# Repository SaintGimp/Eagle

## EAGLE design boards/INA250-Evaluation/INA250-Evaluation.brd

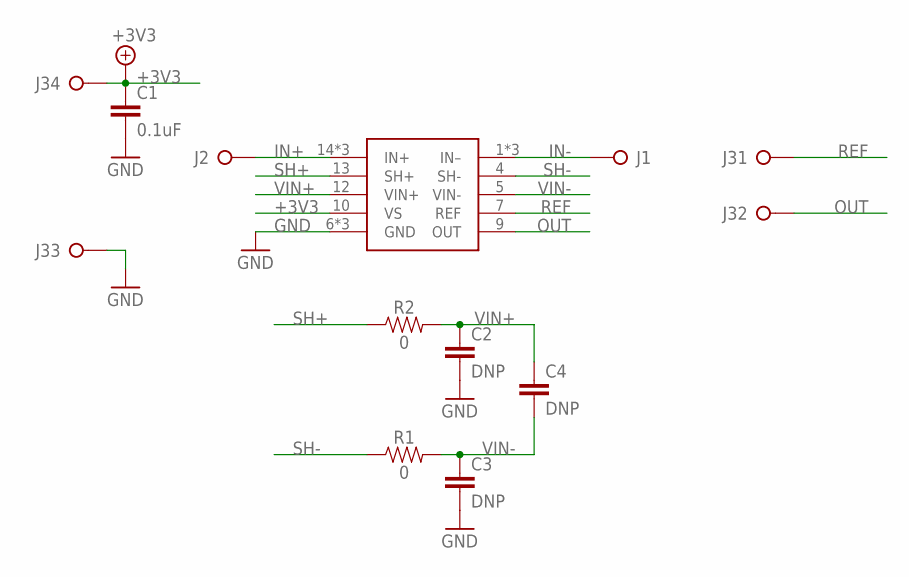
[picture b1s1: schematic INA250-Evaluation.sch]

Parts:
C1: 0.1uF; CAPACITOR-0805
C2, C3, C4: DNP; CAPACITOR-0805
IC1: INA250; TSSOP-16
J1, J2: PINHD-1X1BIG; 1X01-BIG
J3: PINHD-1X4; 1X04
R1, R2: 0; RESISTOR-0805

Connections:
+3V3: C1.1, IC1.10 (VS), J3.4
GND: C1.2, C2.2, C3.2, IC1.6 (GND), IC1.8 (GND), IC1.11 (GND), J3.3
IN+: IC1.14 (IN+), IC1.15 (IN+), IC1.16 (IN+), J2.1
IN-: IC1.1 (IN–), IC1.2 (IN–), IC1.3 (IN–), J1.1
OUT: IC1.9 (OUT), J3.2
REF: IC1.7 (REF), J3.1
SH+: IC1.13 (SH+), R2.1
SH-: IC1.4 (SH-), R1.1
VIN+: C2.1, C4.1, IC1.12 (VIN+), R2.2
VIN-: C3.1, C4.2, IC1.5 (VIN-), R1.2

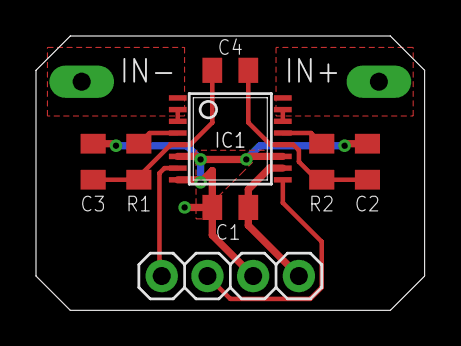
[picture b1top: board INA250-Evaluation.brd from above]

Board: 2 copper layers, 21.6 x 15.2 mm, 10 parts (0 on the bottom side), 10 nets.

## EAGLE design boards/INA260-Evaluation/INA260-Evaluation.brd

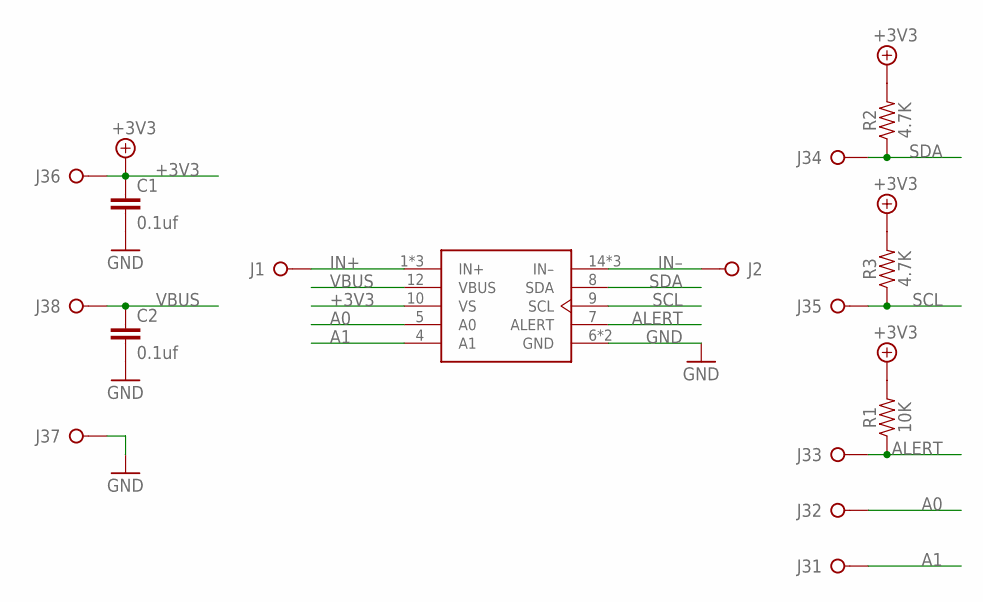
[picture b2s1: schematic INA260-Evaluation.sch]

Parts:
C1, C2: 0.1uf; CAPACITOR-0805
IC1: INA260; TSSOP-16
J1, J2: PINHD-1X1BIG; 1X01-BIG
J3: PINHD-1X8; 1X08
R1: 10K; RESISTOR-0805
R2, R3: 4.7K; RESISTOR-0805

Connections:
+3V3: C1.1, IC1.10 (VS), J3.6, R1.2, R2.2, R3.2
A0: IC1.5 (A0), J3.2
A1: IC1.4 (A1), J3.1
ALERT: IC1.7 (ALERT), J3.3, R1.1
GND: C1.2, C2.2, IC1.6 (GND), IC1.11 (GND), J3.7
IN+: IC1.1 (IN+), IC1.2 (IN+), IC1.3 (IN+), J1.1
IN–: IC1.14 (IN–), IC1.15 (IN–), IC1.16 (IN–), J2.1
SCL: IC1.9 (SCL), J3.5, R3.1
SDA: IC1.8 (SDA), J3.4, R2.1
VBUS: C2.1, IC1.12 (VBUS), J3.8

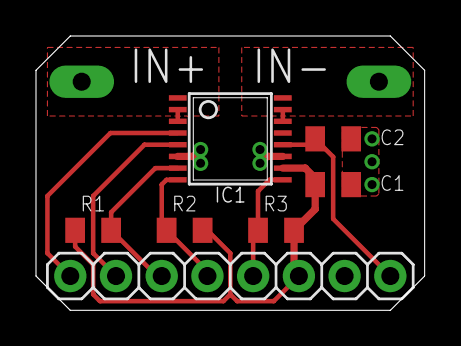
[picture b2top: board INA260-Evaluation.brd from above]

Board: 2 copper layers, 21.6 x 15.2 mm, 9 parts (0 on the bottom side), 10 nets.

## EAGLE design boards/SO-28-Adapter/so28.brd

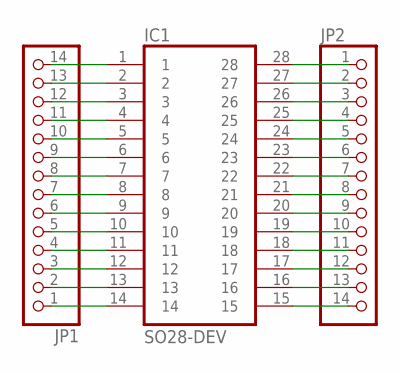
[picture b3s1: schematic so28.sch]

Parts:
IC1: SO28-DEV; SO28W
JP1, JP2: PINHD-1X14; 1X14

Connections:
unnamed: IC1.1, JP1.14
unnamed: IC1.2, JP1.13
unnamed: IC1.3, JP1.12
unnamed: IC1.4, JP1.11
unnamed: IC1.5, JP1.10
unnamed: IC1.6, JP1.9
unnamed: IC1.7, JP1.8
unnamed: IC1.8, JP1.7
unnamed: IC1.9, JP1.6
unnamed: IC1.10, JP1.5
unnamed: IC1.11, JP1.4
unnamed: IC1.12, JP1.3
unnamed: IC1.13, JP1.2
unnamed: IC1.14, JP1.1
unnamed: IC1.15, JP2.14
unnamed: IC1.16, JP2.13
unnamed: IC1.17, JP2.12
unnamed: IC1.18, JP2.11
unnamed: IC1.19, JP2.10
unnamed: IC1.20, JP2.9
unnamed: IC1.21, JP2.8
unnamed: IC1.22, JP2.7
unnamed: IC1.23, JP2.6
unnamed: IC1.24, JP2.5
unnamed: IC1.25, JP2.4
unnamed: IC1.26, JP2.3
unnamed: IC1.27, JP2.2
unnamed: IC1.28, JP2.1

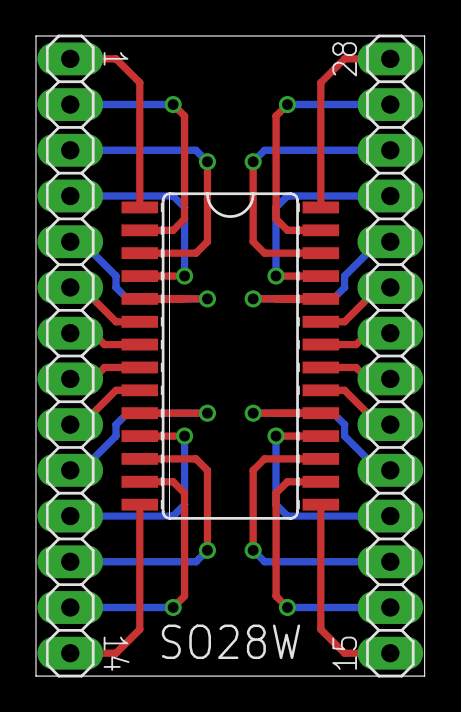
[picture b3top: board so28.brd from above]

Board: 2 copper layers, 21.6 x 35.6 mm, 3 parts (0 on the bottom side), 28 nets.

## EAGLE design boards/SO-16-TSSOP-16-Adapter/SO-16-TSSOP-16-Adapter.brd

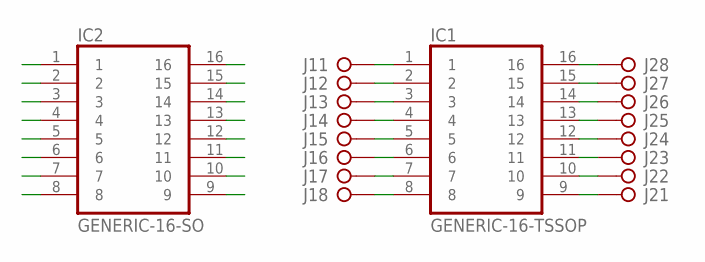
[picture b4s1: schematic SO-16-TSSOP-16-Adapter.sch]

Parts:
IC1: GENERIC-16-TSSOP; TSSOP-16
IC2: GENERIC-16-SO; SO-16
J1, J2: PINHD-1X8; 1X08

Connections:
unnamed: IC1.1, IC2.16, J1.1
unnamed: IC1.2, IC2.15, J1.2
unnamed: IC1.3, IC2.14, J1.3
unnamed: IC1.4, IC2.13, J1.4
unnamed: IC1.5, IC2.12, J1.5
unnamed: IC1.6, IC2.11, J1.6
unnamed: IC1.7, IC2.10, J1.7
unnamed: IC1.8, IC2.9, J1.8
unnamed: IC1.9, IC2.8, J2.1
unnamed: IC1.10, IC2.7, J2.2
unnamed: IC1.11, IC2.6, J2.3
unnamed: IC1.12, IC2.5, J2.4
unnamed: IC1.13, IC2.4, J2.5
unnamed: IC1.14, IC2.3, J2.6
unnamed: IC1.15, IC2.2, J2.7
unnamed: IC1.16, IC2.1, J2.8

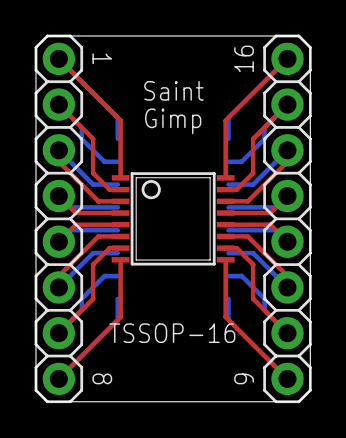
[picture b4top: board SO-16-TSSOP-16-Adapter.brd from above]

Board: 2 copper layers, 15.2 x 20.3 mm, 4 parts (1 on the bottom side), 16 nets.

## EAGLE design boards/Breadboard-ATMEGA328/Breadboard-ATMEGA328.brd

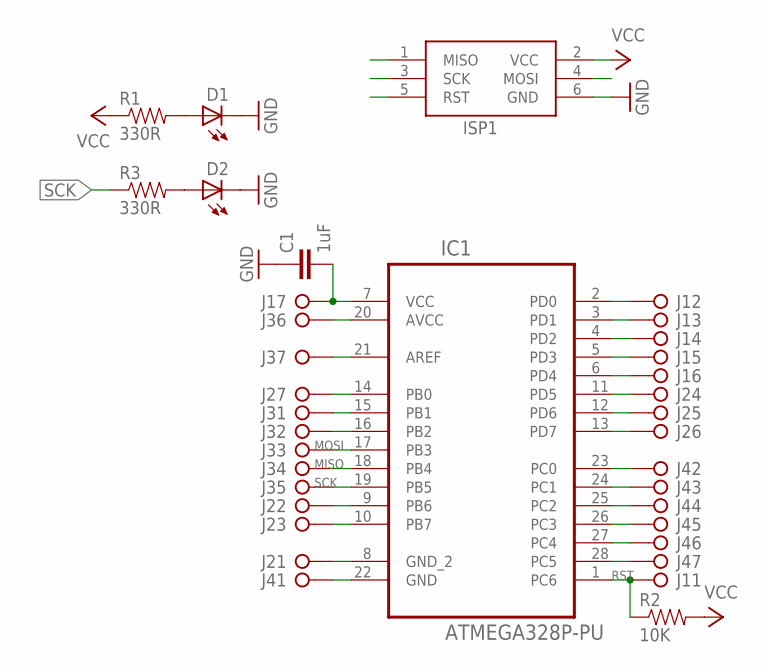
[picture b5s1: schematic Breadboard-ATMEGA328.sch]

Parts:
C1: 1uF; CAPACITOR-0805
D1, D2: LED-0805
IC1: ATMEGA328P-PU; DIP28
ISP1: ICSP-HEADER-6; ICSP-HEADER
J1, J2, J3, J4: PINHD-1X7; 1X07
R1, R3: 330R; RESISTOR-0805
R2: 10K; RESISTOR-0805

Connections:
GND: C1.1, D1.2 (C), D2.2 (C), IC1.8 (GND_2), ISP1.6 (GND), J2.1
MISO: IC1.18 (PB4), ISP1.1 (MISO), J3.4
MOSI: IC1.17 (PB3), ISP1.4 (MOSI), J3.3
unnamed: IC1.22 (GND), J4.1
unnamed: IC1.2 (PD0), J1.2
unnamed: IC1.3 (PD1), J1.3
unnamed: IC1.4 (PD2), J1.4
unnamed: IC1.5 (PD3), J1.5
unnamed: IC1.6 (PD4), J1.6
unnamed: D1.1 (A), R1.2
unnamed: D2.1 (A), R3.2
unnamed: IC1.9 (PB6), J2.2
unnamed: IC1.10 (PB7), J2.3
unnamed: IC1.11 (PD5), J2.4
unnamed: IC1.12 (PD6), J2.5
unnamed: IC1.13 (PD7), J2.6
unnamed: IC1.14 (PB0), J2.7
unnamed: IC1.15 (PB1), J3.1
unnamed: IC1.16 (PB2), J3.2
unnamed: IC1.21 (AREF), J3.7
unnamed: IC1.23 (PC0), J4.2
unnamed: IC1.24 (PC1), J4.3
unnamed: IC1.25 (PC2), J4.4
unnamed: IC1.26 (PC3), J4.5
unnamed: IC1.27 (PC4), J4.6
unnamed: IC1.28 (PC5), J4.7
RST: IC1.1 (PC6), ISP1.5 (RST), J1.1, R2.1
SCK: IC1.19 (PB5), ISP1.3 (SCK), J3.5, R3.1
VCC: C1.2, IC1.7 (VCC), IC1.20 (AVCC), ISP1.2 (VCC), J1.7, J3.6, R1.1, R2.2

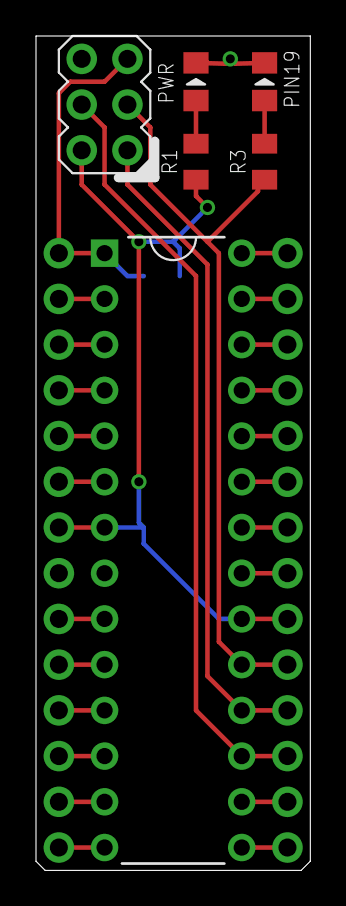
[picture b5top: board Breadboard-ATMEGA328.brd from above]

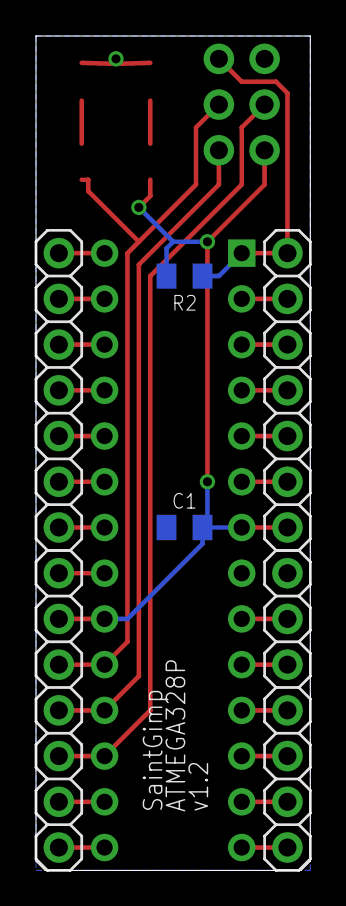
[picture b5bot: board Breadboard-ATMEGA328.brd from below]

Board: 2 copper layers, 15.2 x 46.4 mm, 12 parts (6 on the bottom side), 29 nets.

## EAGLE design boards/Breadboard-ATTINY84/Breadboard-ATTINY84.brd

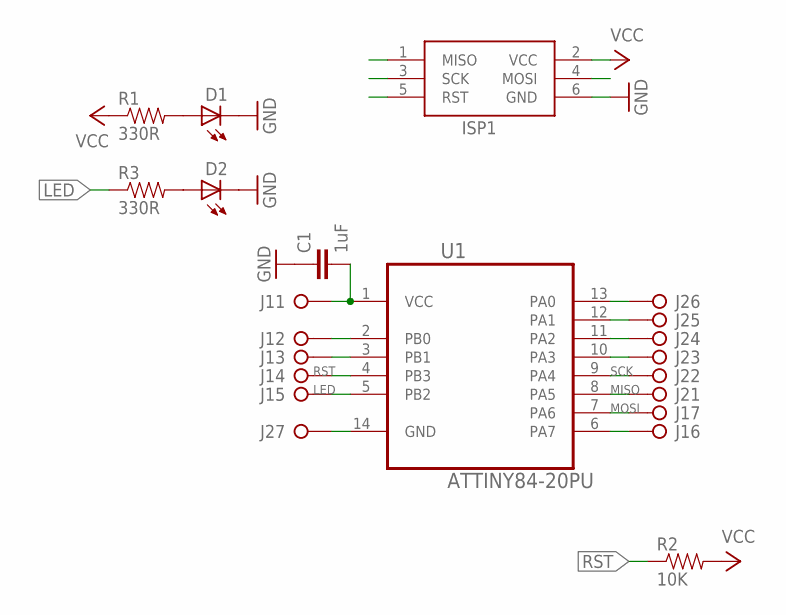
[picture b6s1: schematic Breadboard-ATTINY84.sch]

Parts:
C1: 1uF; CAPACITOR-0805
D1, D2: LED-0805
ISP1: ICSP-HEADER-6; ICSP-HEADER
J1, J2: PINHD-1X7; 1X07
R1, R3: 330R; RESISTOR-0805
R2: 10K; RESISTOR-0805
U1: ATTINY84-20PU; DIP14

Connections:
GND: C1.1, D1.2 (C), D2.2 (C), ISP1.6 (GND), J2.7, U1.14 (GND)
LED: J1.5, R3.1, U1.5 (PB2)
MISO: ISP1.1 (MISO), J2.1, U1.8 (PA5)
MOSI: ISP1.4 (MOSI), J1.7, U1.7 (PA6)
unnamed: D2.1 (A), R3.2
unnamed: J1.2, U1.2 (PB0)
unnamed: J1.3, U1.3 (PB1)
unnamed: J1.6, U1.6 (PA7)
unnamed: D1.1 (A), R1.2
unnamed: J2.3, U1.10 (PA3)
unnamed: J2.4, U1.11 (PA2)
unnamed: J2.5, U1.12 (PA1)
unnamed: J2.6, U1.13 (PA0)
RST: ISP1.5 (RST), J1.4, R2.1, U1.4 (PB3)
SCK: ISP1.3 (SCK), J2.2, U1.9 (PA4)
VCC: C1.2, ISP1.2 (VCC), J1.1, R1.1, R2.2, U1.1 (VCC)

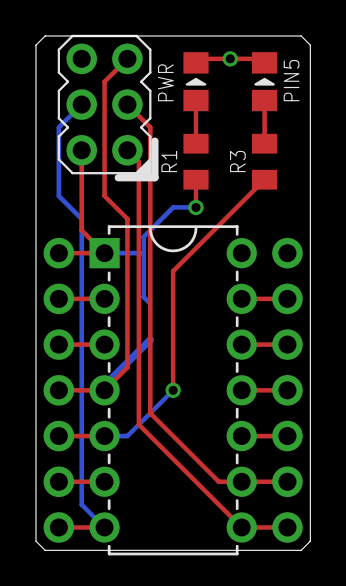
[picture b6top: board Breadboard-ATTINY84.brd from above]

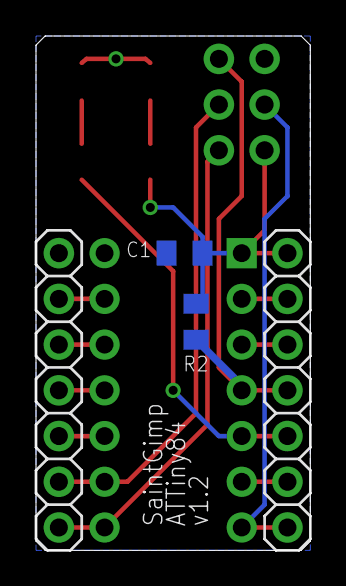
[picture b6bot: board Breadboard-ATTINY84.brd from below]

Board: 2 copper layers, 15.2 x 28.6 mm, 10 parts (4 on the bottom side), 16 nets.

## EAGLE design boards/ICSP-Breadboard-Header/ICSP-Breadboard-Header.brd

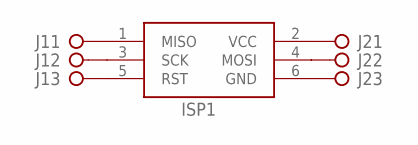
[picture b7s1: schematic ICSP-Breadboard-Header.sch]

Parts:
ISP1: ICSP-HEADER-6; ICSP-HEADER
J1, J2: PINHD-1X3; 1X03

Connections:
unnamed: ISP1.1 (MISO), J1.1
unnamed: ISP1.3 (SCK), J1.2
unnamed: ISP1.5 (RST), J1.3
unnamed: ISP1.2 (VCC), J2.1
unnamed: ISP1.4 (MOSI), J2.2
unnamed: ISP1.6 (GND), J2.3

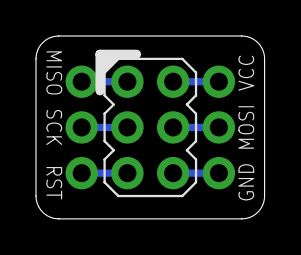
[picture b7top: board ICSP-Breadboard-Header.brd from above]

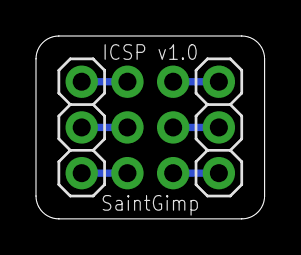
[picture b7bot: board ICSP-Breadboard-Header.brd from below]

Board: 2 copper layers, 12.7 x 10.2 mm, 3 parts (2 on the bottom side), 6 nets.

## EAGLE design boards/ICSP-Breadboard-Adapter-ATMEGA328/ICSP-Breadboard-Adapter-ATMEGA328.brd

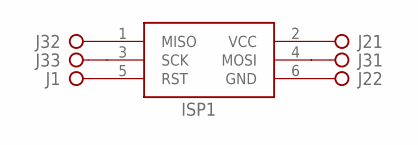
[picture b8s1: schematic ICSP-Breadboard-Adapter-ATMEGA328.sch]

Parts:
ISP1: ICSP-HEADER-6; ICSP-HEADER
J1: PINHD-1X1; 1X01
J2: PINHD-1X2; 1X02
J3: PINHD-1X3; 1X03

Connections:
GND: ISP1.6 (GND), J2.2
unnamed: ISP1.5 (RST), J1.1
unnamed: ISP1.2 (VCC), J2.1
unnamed: ISP1.4 (MOSI), J3.1
unnamed: ISP1.1 (MISO), J3.2
unnamed: ISP1.3 (SCK), J3.3

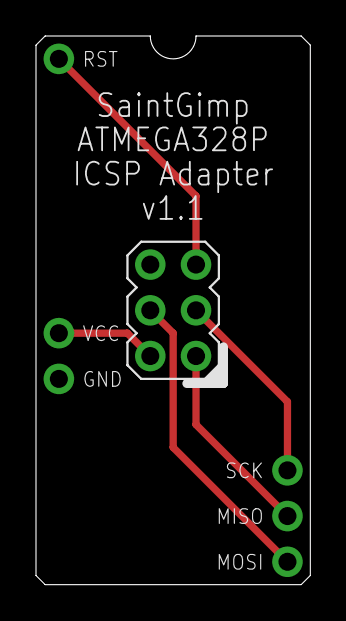
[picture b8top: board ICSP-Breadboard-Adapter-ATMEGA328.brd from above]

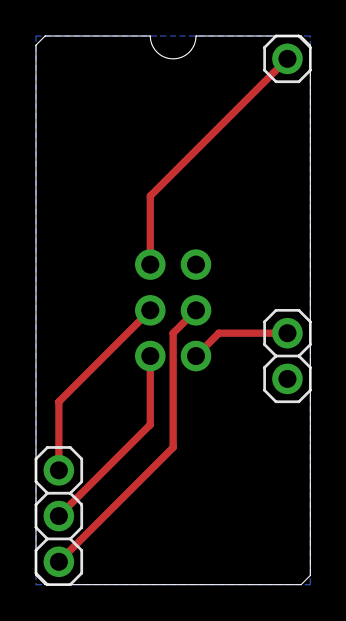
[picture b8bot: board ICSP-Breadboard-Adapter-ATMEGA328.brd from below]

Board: 2 copper layers, 15.2 x 30.5 mm, 4 parts (3 on the bottom side), 6 nets.

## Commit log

2015-03-18 Initial commit of EAGLE library
2015-03-26 refinements
2015-04-08 Updated parts
2015-05-28 More terminal blocks and other changes
2015-05-29 Add dru file
2015-08-02 Many new devices and improvements
2015-08-16 SOT-23-8 adapter board
2015-08-16 New and updated library parts
2015-08-28 Update design rules for masks and restrings
2015-08-28 New library packages
2015-08-28 Fixed SOT-23-8 adapter to have right footprint, and added SOIC-8
2015-12-03 LTC4365 evaluation board
2015-12-03 Updated design rules and library
2016-01-15 Several boards for breadboard prototyping
2016-01-15 Updated breadboard ATTiny84
2016-01-15 Updated breadboard ATMega328
2016-02-15 Library tweaks
2016-02-15 Breadboard adapter for NRF24L01 radio
2016-02-15 Tweaks for various boards
2016-03-24 More library updates
2016-06-26 Library upgrades
2016-10-29 Add a bit of space to breadboard adapters to ICSP connector will fit
2016-10-29 Add SO-16/TSSOP-16 breadboard adapter
2016-10-29 Add SO-28 adapter
2017-02-03 Added and updated parts in library
2017-03-03 Library updates
2018-08-27 Update design rules and library
2020-01-09 Update personal library
2020-01-09 Add evaluation boards for INA250 and 260
